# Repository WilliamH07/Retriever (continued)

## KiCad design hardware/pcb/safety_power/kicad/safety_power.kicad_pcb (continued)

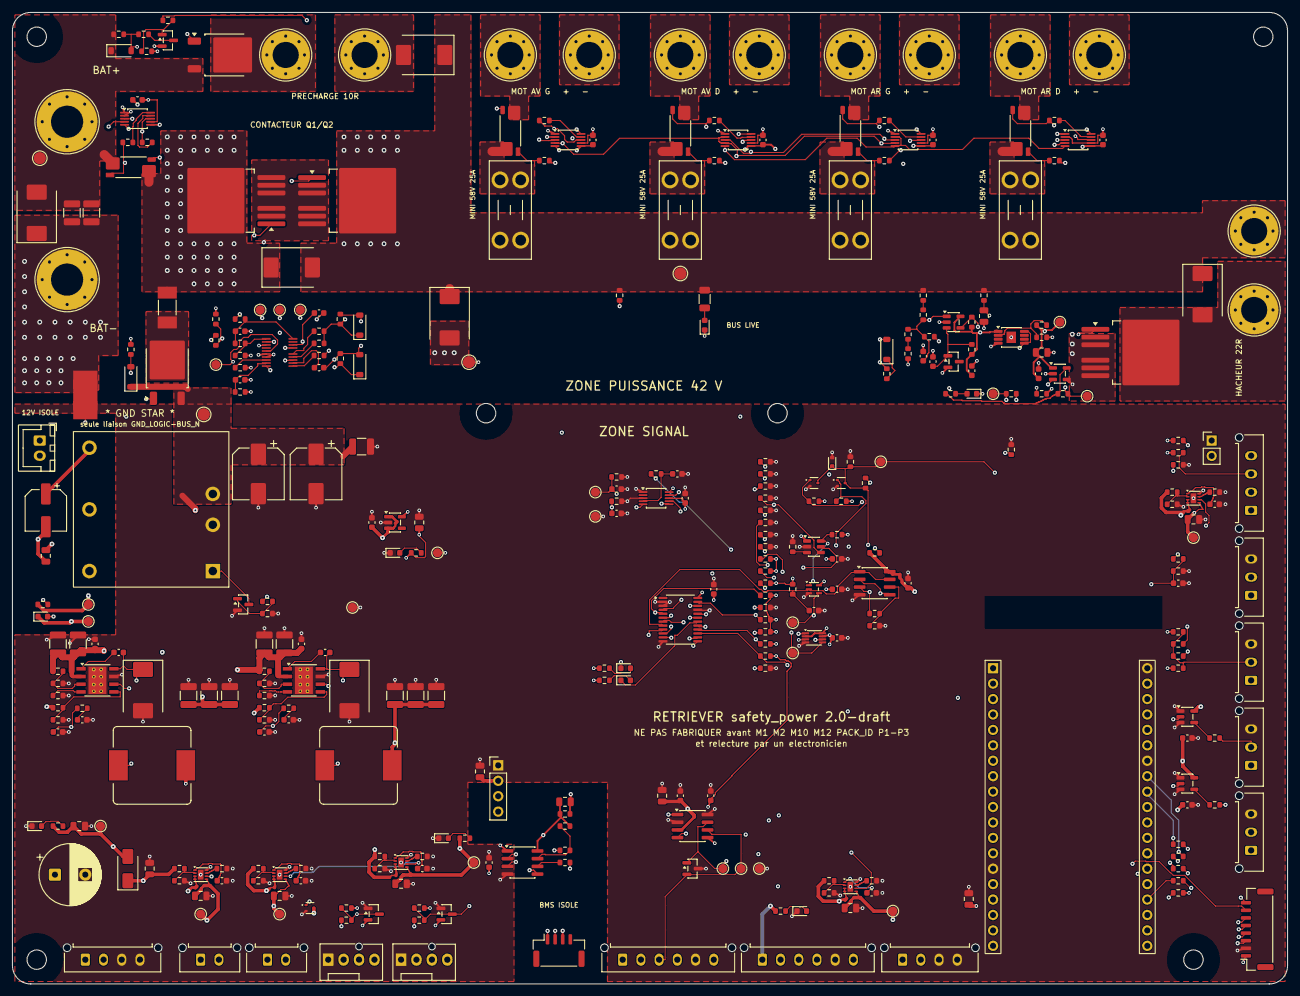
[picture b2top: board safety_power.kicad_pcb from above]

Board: 4 copper layers, 210.0 x 160.0 mm, 350 parts (0 on the bottom side), 190 nets.

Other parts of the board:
H1, H2, H3, H4, H5, H6: M3; MountingHole_3.2mm_M3

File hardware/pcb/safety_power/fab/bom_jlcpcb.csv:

Comment,Designator,Footprint,LCSC Part #
2.2µF 100V,"C1,C2,C51,CB121,CB122,CB51,CB52",C_1210_3225Metric,C153036
10µF 25V,"C10,C171,C181,C191,C201,C211,C52,C54,C57,C60,C78,C98",C_0805_2012Metric,C15850
100nF,"C11,C13,C40,C41,C42,C43,C62,C63,C64,C65,C67,C69,C71,C72,C73,C74,C75,C76,C79,C8,CB124,CB54",C_0603_1608Metric,C14663
1nF,"C12,C68",C_0603_1608Metric,C1588
1µF 25V,"C14,C53,C66,C7",C_0603_1608Metric,C5673
10nF,"C170,C180,C190,C200,C210,C70",C_0603_1608Metric,C57112
100nF 100V,"C4,CB123,CB53",C_0603_1608Metric,C88219
6.8nF,C5,C_0603_1608Metric,C1631
47µF 100V,"C50,C55",CP_Elec_8x10,C48935391
100µF 25V,C56,CP_Elec_6.3x7.7,C2836443
4.7µF 25V,"C61,C77",C_0805_2012Metric,C1779
1µF 100V,C9,C_0805_2012Metric,C385977
2200µF 10V,C99,CP_Radial_D10.0mm_P5.00mm,C49256788
15nF,CB125,C_0603_1608Metric,C107076
82pF C0G,"CB126,CB56",C_0603_1608Metric,C107056
22µF 25V,"CB127,CB128,CB129",C_1210_3225Metric,C52306
8.2nF,CB55,C_0603_1608Metric,C1322360
47µF 10V,"CB57,CB58,CB59",C_1210_3225Metric,C84494
SMCJ48CA,"D1,D2",D_SMC,C151287
KT-0603R,"D10,D11,D22",LED_0603_1608Metric,C2286
BZT52C12,"D12,D6",D_SOD-123,C43491
Everlight 19-217/GHC,"D13,D14,D15,D16,D17,D21",LED_0603_1608Metric,C72043
SS34,D18,D_SMA,C8678
NUP2105L,D19,SOT-23,C14486
ESD5Z3.3,D20,D_SOD-523,C397781
BAT54S,"D23,D24",SOT-23,C19726
B5819W,D26,D_SOD-123,C8598
SS510C,"D3,D7,D8",D_SMC,C19229
BZT52C15,"D4,D5",D_SOD-123,C173427
LM4040A25,D9,SOT-23,C9421
B560C,"DB12,DB5",D_SMC,C85100
5A 125V slo,F5,Fuse_Littelfuse-NANO2-451_453,C66503
Molex 43650-0415,"J11,J8,J9",Molex_Micro-Fit_3.0_43650-0415_1x04_P3.00mm_Vertical,C293547
Molex 43650-0315,"J14,J19,J20,J21",Molex_Micro-Fit_3.0_43650-0315_1x03_P3.00mm_Vertical,C293546
Molex 43650-0615,"J15,J16",Molex_Micro-Fit_3.0_43650-0615_1x06_P3.00mm_Vertical,C505231
IMU_BNO085,J17,JST_GH_SM08B-GHS-TB_1x08-1MP_P1.25mm_Horizontal,C265111
Molex 47053-1000,"J18A,J18B",FanPinHeader_1x04_P2.54mm_Vertical,C240840
BMS_UART (iso),J2,JST_GH_SM04B-GHS-TB_1x04-1MP_P1.25mm_Horizontal,C189895
Molex 43650-0215,"J22,J23",Molex_Micro-Fit_3.0_43650-0215_1x02_P3.00mm_Vertical,C293740
PWR_12V_COMPUTE,J7,JST_XH_B2B-XH-A_1x02_P2.50mm_Vertical,C265283
RADIO E-STOP,JP1,PinHeader_1x02_P2.54mm_Vertical,C492401
33µH,LB12,L_TaiTech_TMPC1265_13.5x12.5mm,C2847586
15µH,LB5,L_TaiTech_TMPC1265_13.5x12.5mm,C189912
URB4812YMD-30WR3,PS1,Mornsun_URB_YMD-30WR3_1x1in,C22458769
B0503S-1WR3,PS2,PinHeader_1x04_P2.54mm_Vertical,C5369462
IPB017N10N5LF,"Q1,Q2,Q5",TO-263-7_TabPin4_NoPin4,C3289286
DMG1012T,"Q10,Q8,Q9",SOT-523,C20512
SUD50P10-43L,"Q3,Q6",TO-252-2,C41408040
MMBT5551,"Q4,Q7",SOT-23,C2145
10Ω,"R1,R13,R14,R19,R29,R40,R41,R44,R45,R48,R49,R52,R53,R6",R_0603_1608Metric,C22859
100k,"R10,R100,R11,R110,R119,R120,R121,R122,R123,R124,R125,R126,R127,R132,R142,R18,R30,R31,R5,R62,R66,R80,R9,R90",R_0603_1608Metric,C25803
47k,"R101,R111,R81,R91",R_0603_1608Metric,C25819
4.42k,"R102,R112",R_0603_1608Metric,C23043
150k,"R12,R60",R_0603_1608Metric,C22807
10k,"R128,R129,R130,R131,R135,R136,R138,R140,R141,R145,R146,R147,R15,R153,R154,R165,R171,R173,R175,R21,R22,R28,R65,R71",R_0603_1608Metric,C25804
2.2k,"R133,R134,R92",R_0603_1608Metric,C4190
1k,"R137,R139,R143,R152,R155,R156,R63,R64,R85",R_0603_1608Metric,C21190
5.23k,R144,R_0603_1608Metric,C23068
20k,R148,R_0603_1608Metric,C4184
57.6k,R149,R_0603_1608Metric,C23082
18.7k,R150,R_0603_1608Metric,C22893
24.3k,R151,R_0603_1608Metric,C23348
0R,"R158,R26",R_0603_1608Metric,C21189
22k,R16,R_0603_1608Metric,C31850
33Ω,"R161,R162,R163,R164",R_0603_1608Metric,C23140
470Ω,"R166,R167",R_0603_1608Metric,C23179
330Ω,"R168,R34",R_0603_1608Metric,C23138
100Ω,"R169,R170",R_0603_1608Metric,C22775
4.7k,"R17,R172,R174,R33,R67,R75",R_0603_1608Metric,C23162
1M,R2,R_0603_1608Metric,C22935
93.1k,R20,R_0603_1608Metric,C228101
49.9k 0.1%,"R23,R24",R_0603_1608Metric,C2828622
6.19k 0.1%,R25,R_0603_1608Metric,C667011
1.69M,R27,R_0603_1608Metric,C247054
51k,R3,R_0603_1608Metric,C23196
33k,R32,R_0603_1608Metric,C4216
40.2k,R4,R_0603_1608Metric,C12447
22k,R61,R_1206_3216Metric,C114942
150Ω,"R7,R8",R_0603_1608Metric,C22808
124k,R70,R_0603_1608Metric,C22788
1.05k,R72,R_0603_1608Metric,C858882
1.4k,R82,R_0603_1608Metric,C25957
1.18M,"RB121,RB51",R_0603_1608Metric,C4072929
59k,"RB122,RB52",R_0603_1608Metric,C23085
243k,"RB123,RB53",R_0603_1608Metric,C23351
143k,RB124,R_0603_1608Metric,C304703
10.2k,"RB125,RB55",R_0603_1608Metric,C22772
10.5k,RB126,R_0603_1608Metric,C22855
53.6k,RB54,R_0603_1608Metric,C23074
10.7k,RB56,R_0603_1608Metric,C22857
1mΩ WSK2512,RS1,R_Shunt_Vishay_WSK2512_6332Metric_T1.19mm,C4248455
2mΩ WSK2512,"RS2,RS3,RS4,RS5",R_Shunt_Vishay_WSK2512_6332Metric_T1.19mm,C3997408
TPS48100QDGXRQ1,U1,TI_DGX0019A_VSSOP-19,C43131316
TPS259573,U10,Texas_DSG0008A_WSON-8-1EP_2x2mm_P0.5mm_EP0.9x1.6mm,C2653844
TPS259531,"U11,U12,U13,U14",Texas_DSG0008A_WSON-8-1EP_2x2mm_P0.5mm_EP0.9x1.6mm,C2155674
TCAN1042HVDRQ1,U16,SOIC-8_3.9x4.9mm_P1.27mm,C485807
TPL5010,U17,SOT-23-6,C473912
74LVC1G08,U18,SOT-353_SC-70-5,C12512
SN74LVC1G74,U19,VSSOP-8_2.3x2mm_P0.5mm,C70285
INA228,"U2,U6,U7,U8,U9",TSSOP-10_3x3mm_P0.5mm,C2887910
LM2903,U20,SOIC-8_3.9x4.9mm_P1.27mm,C7549
ADS1115,U21,TSSOP-10_3x3mm_P0.5mm,C37593
TCA9555,U22,TSSOP-24_4.4x7.8mm_P0.65mm,C465732
74AHCT1G125,"U23,U24",SOT-23-5,C7484
ADuM1201,U25,SOIC-8_3.9x4.9mm_P1.27mm,C9669
AP2112K-3.3,U26,SOT-23-5,C51118
TPS7A4001,U3,HVSSOP-8-1EP_3x3mm_P0.65mm_EP1.57x1.89mm,C5144143
TLV1701,U4,SOT-23-5,C130035
UCC27517,U5,SOT-23-5,C99395
TPS54360BDDAR,"UB12,UB5",TI_SO-PowerPAD-8_ThermalVias,C524806
